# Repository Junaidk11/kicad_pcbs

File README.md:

# kicad_pcbs

Developed a sudden interest in PCB design, will upload all my PCB design projects here using kiCAD 

## First PCB: Traffic Light

## Second PCB: A 4-Layer PCB with STM32 + BUCK CONVERTER + USB

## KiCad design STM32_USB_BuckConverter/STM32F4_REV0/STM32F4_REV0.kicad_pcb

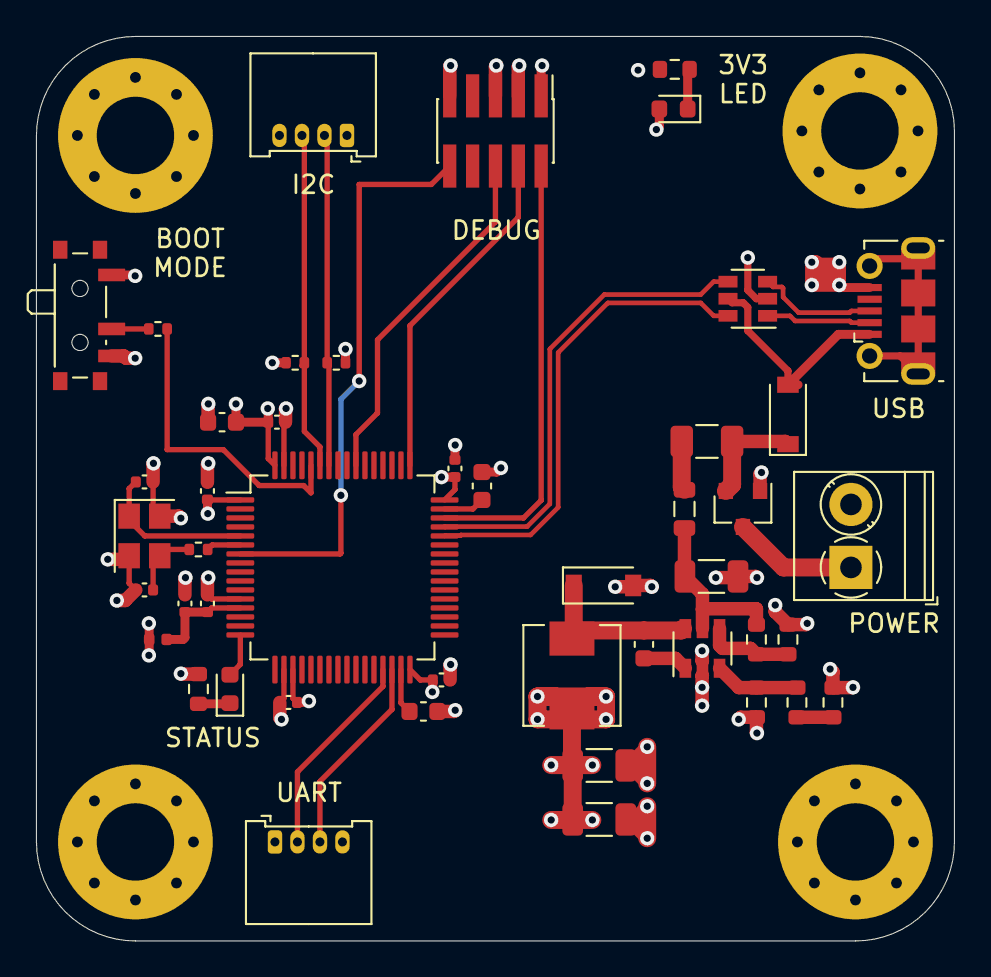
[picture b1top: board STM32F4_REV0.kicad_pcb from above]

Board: 4 copper layers, 51.0 x 50.2 mm, 50 parts (0 on the bottom side), 35 nets.

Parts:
C1, C3, C4: 10u; C_1206_3216Metric
C2: 10n; C_0603_1608Metric
C5: 4u7; C_0603_1608Metric
C6, C7, C8, C9, C10: 100n; C_0402_1005Metric
C11: 1u; C_0402_1005Metric
C12: 10n; C_0402_1005Metric
C13, C14: 2u2; C_0603_1608Metric
C15, C16: 12p; C_0402_1005Metric
D1, D2: B5819W; D_SOD-123
D3: RED; LED_0603_1608Metric
D4: BLUE; LED_0603_1608Metric
F1: 250mA; Fuse_1206_3216Metric
FB1: 600 @ 600MHz; L_0805_2012Metric
H1, H2, H3, H4: MountingHole_Pad; MountingHole_4.3mm_M4_Pad_Via
J1: Screw_Terminal_01x02; TerminalBlock_Phoenix_PT-1,5-2-3.5-H_1x02_P3.50mm_Horizontal
J2: SWD; PinHeader_2x05_P1.27mm_Vertical_SMD
J3, J4: Conn_01x04; Molex_PicoBlade_53048-0410_1x04_P1.25mm_Horizontal
J5: USB_B_Micro; USB_Micro-B_Molex-105017-0001
L1: 10u; L_Sunlord_MWSA0518_5.4x5.2mm
L2: 39n; L_0402_1005Metric
Q1: AO3401A; SOT-23
R1: 100k; R_0603_1608Metric
R2: 68k; R_0603_1608Metric
R3: 47k; R_0603_1608Metric
R4: 15k; R_0603_1608Metric
R5: 270; R_0603_1608Metric
R6: 1k; R_0603_1608Metric
R7: 10k; R_0402_1005Metric
R8: 47; R_0402_1005Metric
R9: 1k5; R_0603_1608Metric
R10, R11: 2k2; R_0402_1005Metric
SW1: SW_SPDT; SW_SPDT_PCM12
U1: MP2359DJ-LF-Z; SOT-23-6
U2: STM32F405RGT6; LQFP-64_10x10mm_P0.5mm
U3: USBLC6-2SC6; SOT-23-6
Y1: 16MHz; Crystal_SMD_3225-4Pin_3.2x2.5mm

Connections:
+3.3VA: C11.1, C12.1, L2.2, U2.13
+3V3: C3.1, C4.1, C5.1, C6.1, C7.1, C8.1, C9.1, C10.1, D3.2, J2.1, J3.1, J4.1, L1.2, L2.1, R3.1, R10.2, R11.2, SW1.1, U2.1, U2.19, U2.32, U2.48, U2.64
+5V: D1.2, J5.1, U3.5
+12V: J1.1, Q1.3
BOOT0: R7.2, U2.60
BUCK_BST: C2.1, U1.1
BUCK_EN: R1.1, R2.2, U1.4
BUCK_FB: R3.2, R4.1, U1.3
BUCK_IN: C1.1, FB1.2, R1.2, U1.5
BUCK_SW: C2.2, D2.1, L1.1, U1.6
GND: C1.2, C3.2, C4.2, C5.2, C6.2, C7.2, C8.2, C9.2, C10.2, C11.2, C12.2, C13.2, C14.2, C15.2, C16.2, D2.2, H1.1, H2.1, H3.1, H4.1, J1.2, J2.3, J2.5, J2.9, J3.4, J4.4, J5.5, Q1.1, R2.1, R5.2, R6.1, R9.1, SW1.3, U1.2, U2.12, U2.18, U2.63, U3.2, Y1.2, Y1.4
HSE_IN: C15.1, U2.5, Y1.1
HSE_OUT: R8.1, U2.6
I2C1_SCL: J3.2, R11.1, U2.58
I2C1_SDA: J3.3, R10.1, U2.59
LED_STATUS: D4.2, U2.16
NRST: J2.10, U2.7
unnamed: C13.1, U2.31
unnamed: C14.1, U2.47
unnamed: C16.1, R8.2, Y1.3
unnamed: D1.1, F1.1, Q1.2
unnamed: D3.1, R6.2
unnamed: D4.1, R9.2
unnamed: F1.2, FB1.1
unnamed: R4.2, R5.1
unnamed: R7.1, SW1.2
SWCLK: J2.4, U2.49
SWDIO: J2.2, U2.46
SWO: J2.6, U2.55
USART3_RX: J4.3, U2.30
USART3_TX: J4.2, U2.29
USB_CONNECTOR_D+: J5.3, U3.3
USB_CONNECTOR_D-: J5.2, U3.1
USB_D+: U2.45, U3.4
USB_D-: U2.44, U3.6

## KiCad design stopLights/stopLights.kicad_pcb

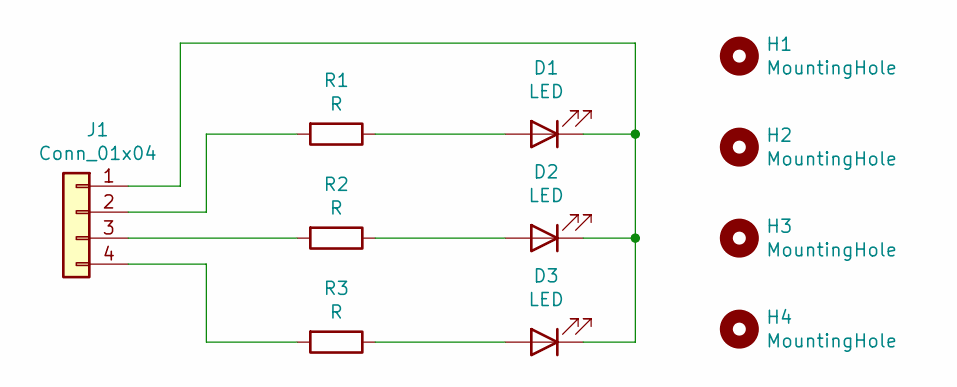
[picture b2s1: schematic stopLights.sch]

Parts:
D1, D2, D3: LED; LED_D3.0mm
H1, H2, H3, H4: MountingHole; MountingHole_2.5mm_Pad
J1: Conn_01x04; PinHeader_1x04_P2.54mm_Horizontal
R1, R2, R3: R; R_Axial_DIN0204_L3.6mm_D1.6mm_P5.08mm_Horizontal

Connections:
unnamed: D1.1 (K), D2.1 (K), D3.1 (K), J1.1
unnamed: D1.2 (A), R1.1
unnamed: D2.2 (A), R2.1
unnamed: D3.2 (A), R3.1
unnamed: J1.2, R1.2
unnamed: J1.3, R2.2
unnamed: J1.4, R3.2

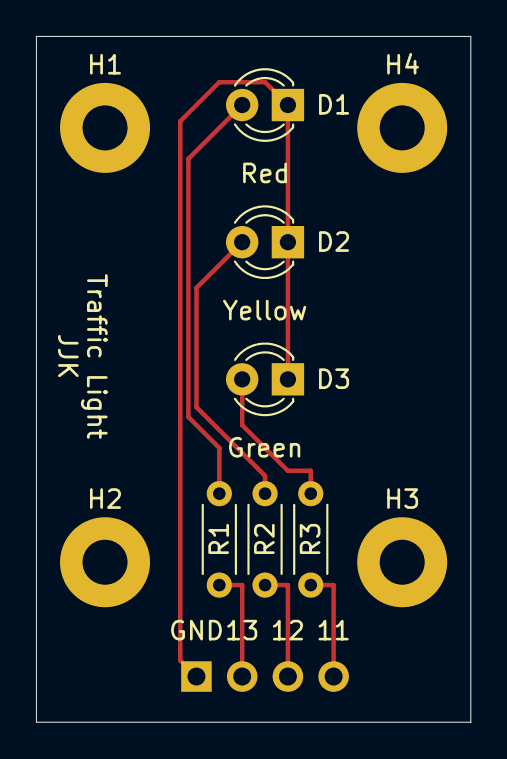
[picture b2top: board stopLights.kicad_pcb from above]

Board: 2 copper layers, 24.1 x 38.1 mm, 11 parts (1 on the bottom side), 7 nets.

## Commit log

2021-01-23 stop Lights PCB project project and schematic
2021-01-23 moved components into pcb view.
2021-01-23 Added traces.
2021-01-23 reduced size of board.
2021-01-23 Added text on Front silk layer.
2021-03-23 added schematic for buck and STM components.
2021-03-23 Created personal kiCAD symbol library. Added buck converter symbol to the library.
2021-03-23 Added footprints for power connectors and Serial wire debug connector
2021-03-23 Added pull-up resistors to I2C data and clock line.
2021-03-23 Added connectors for I2C and UART modules.
2021-03-23 Added USB micro connector. Also added schottky diode in the power circuitry incase we want to power the board with USB and not the 12V. The schottky diode will protect incase both 12V present and the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
2021-03-23 Added ESD protection component for the USB connector.
2021-03-23 rearranged schematic to make it readable.
2021-03-23 Performed ERC, ignorable warnings rejects.
2021-03-23 Added footprints for all the schematic symbols.
2021-03-23 started PCB layout.
2021-03-24 Updated PCB I2C pins, crystal oscillator setup.
2021-04-05 Finished layout of MCU.
2021-04-06 Finished routing. Added vias for 3v3 and GND.
